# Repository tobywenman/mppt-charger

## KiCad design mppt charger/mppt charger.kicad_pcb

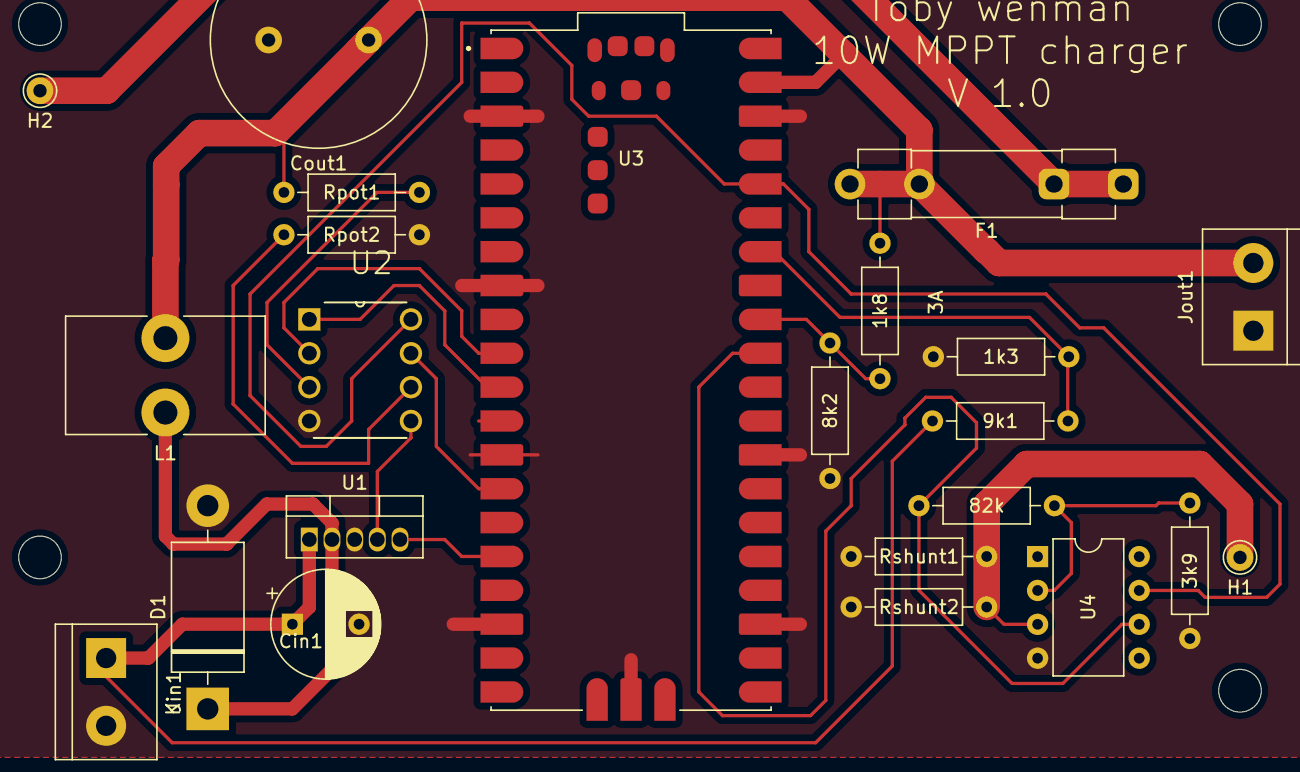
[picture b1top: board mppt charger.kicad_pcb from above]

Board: 2 copper layers, 23 parts (0 on the bottom side), 19 nets.

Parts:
1k3: 1k3; R_Axial_DIN0207_L6.3mm_D2.5mm_P10.16mm_Horizontal
1k8: 1k8; R_Axial_DIN0207_L6.3mm_D2.5mm_P10.16mm_Horizontal
3k9: 3k9; R_Axial_DIN0207_L6.3mm_D2.5mm_P10.16mm_Horizontal
8k2: 8k2; R_Axial_DIN0207_L6.3mm_D2.5mm_P10.16mm_Horizontal
9k1: 9k1; R_Axial_DIN0207_L6.3mm_D2.5mm_P10.16mm_Horizontal
Cin1: 100uF; CP_Radial_D8.0mm_P5.00mm
Cout1: 1000uF; C_Radial_D16.0mm_H25.0mm_P7.50mm
D1: 1N5822; D_DO-201AD_P15.24mm_Horizontal
F1: Fuse; Fuseholder_Clip-5x20mm_Littelfuse_445-030_Inline_P20.50x5.2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
H1, H2: MountingHole_Pad; Pin_D1.0mm_L10.0mm
Jin1: Screw_Terminal_01x02; TerminalBlock_bornier-2_P5.08mm
Jout1: Screw_Terminal_01x02; TerminalBlock_bornier-2_P5.08mm
L1: 100uF; L_Toroid_Vertical_L14.7mm_W8.6mm_P5.58mm_Pulse_KM-1
Rf1: 82k; R_Axial_DIN0207_L6.3mm_D2.5mm_P10.16mm_Horizontal
Rpot1: 12k5; R_Axial_DIN0207_L6.3mm_D2.5mm_P10.16mm_Horizontal
Rpot2: 10k; R_Axial_DIN0207_L6.3mm_D2.5mm_P10.16mm_Horizontal
Rshunt1, Rshunt2: 0R1; R_Axial_DIN0207_L6.3mm_D2.5mm_P10.16mm_Horizontal
U1: LM2576T-ADJ; TO-220-5_Vertical
U2: X9C103P; DIP254P762X533-8
U3: SC0915; MODULE_SC0915
U4: MCP601-xP; DIP-8_W7.62mm

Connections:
+3.3V: U2.8 (VCC), U3.36 (3V3_OUT), U4.7 (V+)
+BATT: F1.1, H2.1
-BATT: H1.1, Rshunt1.1, Rshunt2.1, U4.3 (+)
GND: 1k3.1, 3k9.1, 8k2.1, Cin1.2, Cout1.2, D1.2 (A), Jin1.2, Jout1.1, Rpot2.1, Rshunt1.2, Rshunt2.2, U1.3 (GND), U2.4 (VSS), U3.3 (GND), U3.8 (GND), U3.13 (GND), U3.18 (GND), U3.23 (GND), U3.28 (GND), U3.38 (GND), U3.D2 (GND), U4.4 (V-)
unnamed: 9k1.2, Cin1.1, Jin1.1, U1.1 (VIN)
unnamed: D1.1 (K), L1.1, U1.2 (OUT)
unnamed: 1k8.1, 8k2.2, U3.32 (GP27)
unnamed: 3k9.2, Rf1.2, U4.2 (-)
unnamed: Rf1.1, U3.31 (GP26), U4.6
unnamed: Rpot1.2, U2.3 (VH/RH)
unnamed: Rpot2.2, U2.6 (VL/RL)
unnamed: U1.4 (FB), U2.5 (VW/RW)
unnamed: U1.5 (~ON/OFF), U3.16 (GP12)
unnamed: U2.1 (~INC), U3.11 (GP8)
unnamed: U2.2 (U/~D), U3.10 (GP7)
unnamed: U2.7 (~CS), U3.14 (GP10)
unnamed: U3.A (USB_SHIELD), U3.B (USB_SHIELD), U3.C (USB_SHIELD), U3.D (USB_SHIELD)
VinSense: 1k3.2, 9k1.1, U3.34 (GP28)
Vout: 1k8.2, Cout1.1, F1.2, Jout1.2, L1.2, Rpot1.1, U3.39 (VSYS)

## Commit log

2023-02-08 added output terminal
2023-02-09 version sent for manufacture
2023-02-10 added board edge
